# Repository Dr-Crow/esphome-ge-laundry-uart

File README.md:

# ESPHome GE Laundry UART

Local Home Assistant control and monitoring for compatible GE appliances through ESPHome and the appliance's GEA serial bus.

> [!WARNING]
> The appliance uses an 8P8C modular connector that looks like Ethernet, but it is **not Ethernet**. Do not connect it to network equipment.

The project began as an effort to integrate a GE washer and dryer with Home Assistant. An ESP32 powered by the appliance communication port reports information such as remaining time and cycle completion through ESPHome. Early work involved researching the GEA2 and GEA3 protocols and the U+ Connect module; later, [GE Appliances](https://github.com/geappliances) and [FirstBuild](https://firstbuild.com/inventions/home-assistant-adapter/) published additional hardware and protocol information. The maintained ESPHome implementation now lives in [mguaylam/esphome-gea](https://github.com/mguaylam/esphome-gea), while this repository provides compatible hardware, reference configurations, manufacturing files, and enclosures.

## Getting started

### I already have a board

Follow the [firmware setup guide](firmware/README.md) to choose a GEA2 or GEA3 configuration, flash the board, connect it to Home Assistant, and check the status LEDs. The [Rev 2 enclosure](case/rev2/README.md) includes ready-to-print files.

### I want to review a new board

The selected development focus is the socketed C3/C6 Rev3C with both appliance inputs, automatic priority and rated protection. This integration includes all seven editable board revisions, eight firmware profiles, native validation and the [illustrated Rev3C ordering guide](pcb/rev3c/ORDERING.md). Start with the [current comparison and validation](docs/revision-comparison/README.md), [exact source handoff](docs/revision-comparison/HANDOFF.md) and [finish registry](docs/revision-comparison/FINISH-PLAN.md).

Fresh pinned KiCad 9.0.9 ERC/DRC and intended-rule checks pass for all seven revisions. The [Rev3C stencil correction](pcb/rev3c/STENCIL-REVIEW.md) removes unintended drill-marker openings. Native/CAM agreement is separate from supplier process, appliance power and physical qualification. The corrected Rev3C trio has refreshed October 5 quotes of $134.64 for five or $168.92 for ten assembled carriers, before shipping, tax and XIAO modules; Rev2.2's old $78.07 quote is historical.

Older boards and the complete change history are listed in the [PCB revision index](pcb/README.md). Hardware contributors should also read the [contribution guide](CONTRIBUTING.md).

For the proposed USB-C revisions, see the [board and enclosure comparison](docs/revision-comparison/README.md), including assembled-board estimates and views from several angles. The [project handoff](docs/revision-comparison/HANDOFF.md) records the development branches and remaining work.

## Related projects

- [GE Appliances organization](https://github.com/geappliances)
- [FirstBuild Home Assistant adapter](https://firstbuild.com/inventions/home-assistant-adapter/)
- [puddly/casserole](https://github.com/puddly/casserole)
- [GEMakers/green-bean](https://github.com/GEMakers/green-bean)
- [doitaljosh/gea-interface-board](https://github.com/doitaljosh/gea-interface-board)
- [doitaljosh/ge-appliances-re](https://github.com/doitaljosh/ge-appliances-re)
- [doitaljosh/geabus-documentation](https://github.com/doitaljosh/geabus-documentation)
- [simbaja/gehome](https://github.com/simbaja/gehome)
- [GE Appliances Home Assistant adapter](https://github.com/geappliances/home-assistant-adapter)
- [GE Appliances Home Assistant examples](https://github.com/geappliances/home-assistant-examples)
- [GE Appliances Home Assistant bridge](https://github.com/geappliances/home-assistant-bridge)

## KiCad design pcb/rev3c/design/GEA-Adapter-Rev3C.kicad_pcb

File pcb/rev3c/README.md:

# Selected Rev3C prototype: shared XIAO C3/C6 carrier

D14/D15 now use the reviewed 1 A STPS140Z input OR diode; numbered nets and board routing are retained. [Current part-repair evidence](validation/INPUT-DIODE-REPAIR.md) distinguishes this new source from earlier validation and quote snapshots. Exact new-source checks and supplier matching remain required.

The selected development design uses two **TPS1H200A 40 V-rated switches**, 33 V resettable input fuses, and coordinated review of both GE power branches. It preserves PIN1 and PIN3 inputs, automatic PIN1 priority, the AP63205 buck and all C3/C6 side-header functions. C3 is the first implementation focus; C6 firmware and mechanical flexibility remain. Selection does not qualify the appliance supply, surge energy, loaded startup, thermal behavior or enclosure.

The switch change adds voltage margin against the conditional 26 V SMF16A clamp example that exceeds the former TPS22810’s 20 V absolute input limit. It does not give the entire carrier a 40 V rating or prove that a GE appliance produces that pulse. Read the [rated-input review](RATED-SWITCH-OPTION.md) and [qualification gates](POWER-QUALIFICATION.md).

[PCB revision index](../README.md) · [Gate repair](GATE-PROTECTION.md) · [Power qualification](POWER-QUALIFICATION.md) · [Antenna review](ANTENNA-REVIEW.md) · [Shared firmware](../../firmware/shared-rev3c/README.md)

## Preserved hardware

- Original 99 × 40 mm outline, four copper layers and 1.6 mm board thickness
- Mounting datums at (4.5, 33) and (94, 35) mm
- Factory-populated `J5`/`J6` HCTL PM254-1-07-Z-8.5 female 1×7 sockets and all 14 side-header functions
- GEA2/GEA3 interfaces, LEDs, pull-ups and `JP1`'s default 1–2 bridge
- Both original input branches, corrected reverse-FET/gate networks, selected rated load switches, diode isolation, common AP63205 buck and automatic PIN1 priority

The shared-source omissions are `J2` and `D19`; neither GE power input is removed. The local C6 antenna change adds an all-layer copper exclusion at x77.0–80.9, y11.8–19.2 mm and minimal reroutes of `GEA2_RX`, `GEA2_MCU_TX` and `BOOT_SEL`. The selected rated-switch design preserves the original selection and conversion topology. See the [antenna review](ANTENNA-REVIEW.md) for geometry and limits.

The [KiCad project](design/GEA-Adapter-Rev3C.kicad_pro), [schematic](design/GEA-Adapter-Rev3C.kicad_sch) and [PCB](design/GEA-Adapter-Rev3C.kicad_pcb) are editable review sources. Restoration starts from public Rev3C commit `38d94d3dc7c41692e3c41710ec33b9f6e0c38b3e` and recovered shared schematic blob `2799d9e3f023144f684d708297805eed4f355355`.

## Module and firmware selection

The side-header functions match the [XIAO ESP32-C3](https://wiki.seeedstudio.com/XIAO_ESP32C3_Getting_Started/) and [XIAO ESP32-C6](https://wiki.seeedstudio.com/xiao_esp32c6_getting_started/) references. The module is supplied separately from the assembled carrier. Use a module with all 14 header pins installed, and verify its actual revision, header mating depth and retention before use. This interface review does not establish compatibility with other XIAO models.

The [four shared firmware profiles](../../firmware/shared-rev3c/README.md) cover C3/C6 and GEA2/GEA3. Their GPIO numbers differ by module; the recovered eight YAML sources are unchanged. Keep `JP1` at 1–2 for these GEA2 profiles. The alternate 2–3 position changes TX and reaches C3 BOOT; the corresponding C6 D9 pin is GPIO20, not C6 BOOT.

Insert or remove the module only with all power disconnected. Seat all 14 pins without reversal or row offset; the sockets are unkeyed. Match the module USB connector to the carrier's right edge and orientation mark. Recovery uses the module's own BOOT/RESET buttons and native USB. There is no populated carrier recovery header or auxiliary 5 V recovery input.

## Power and qualification

PIN1 and PIN3 from one appliance are two internally selected input branches. Disconnect the appliance cable before attaching powered USB, and remove USB before appliance use. Both reviewed modules connect side-header VBUS directly to USB receptacle VBUS; carrier diodes do not isolate a connected USB host. Keep UART VCC disconnected. Use module 3V3 only as its output. Do not attach a battery within the reviewed load budget.

The corrected reverse-FET/source-referenced gate networks remain. The rated switches address the old switch/clamp rating mismatch in a bounded positive-pulse comparison, and PIN3 gains its matching TVS. Whole-chain transient/energy/differential limits, source current, current-limit/retry effects, thermal behavior and both modules' nominal5 V loaded startup remain open in [POWER-QUALIFICATION.md](POWER-QUALIFICATION.md). Automatic priority detects PIN1 presence rather than useful output power. No universal appliance compatibility is established.

## Review package and cost

Native KiCad 9.0.9 full-severity [ERC](validation/native-kicad-9.0.9-erc.json) and all-track/[parity DRC](validation/native-kicad-9.0.9-drc.json) report 0 violations,0 unconnected items and0 parity differences. The current [rated-switch proof](validation/rated-switch-proof.json) verifies 100 schematic/PCB items,233 pin nets,205 unchanged nonreplacement pin nets, original core functions/outline/mounts/sockets/firmware and0.0 mm² filled copper in the antenna exclusion on all four layers. The historical restoration/gate proofs describe their frozen checkpoints, not the current rated design's full delta.

The regenerated [BOM](manufacturing/BOM-GEA-Adapter-Rev3C.csv) and [CPL](manufacturing/CPL-GEA-Adapter-Rev3C.csv) each contain 83 matching fitted references,80−C22/C23+R38/R39/R40/R41/D20. The module is supplied separately; DNI D8 stays excluded. The native [Gerber/drill ZIP](manufacturing/GERBER-GEA-Adapter-Rev3C.zip) contains 14 members. The [stencil review](STENCIL-REVIEW.md) removes unintended drill-marker openings while preserving existing SMT apertures; D8's two remaining paste apertures need assembler review. [Schematic](validation/schematic.pdf), [PTH](validation/pth-drill-map.pdf) and [NPTH](validation/npth-drill-map.pdf) review PDFs are refreshed.

Current copper views: [front](images/rev3c-copper-f-cu.svg), [inner ground](images/rev3c-copper-in1-cu.svg), [inner routing](images/rev3c-copper-in2-cu.svg), [bottom](images/rev3c-copper-b-cu.svg). Current native partial previews: [C3 top](images/rev3c-render-top.png), [bottom](images/rev3c-render-bottom.png), [C3 oblique](images/rev3c-render-oblique.png), [C6 alternative](images/rev3c-render-c6-oblique.png). The [component model accuracy checkpoint](MODEL-ACCURACY.md) explains the revision-specific official PCB-derived C3/C6 geometry, generic USB/package substitutions, omitted module parts, drawing-based RJ45/socket detail and provisional installed height. Complete manufacturer assembly CAD was not verified; shield/buttons/antenna/male headers are omitted; a separately registered nominal U.FL reference is included and switch/PPTC maximum envelopes remain. Actual pixels were inspected. The [electrical preservation receipt](validation/component-model-electrical-preservation.json) proves that this model lane leaves all electrical source, manufacturing files and firmware unchanged.

Complete exact-part JLCPCB quotes refreshed on October 5, 2026 against the current stencil-corrected trio are **$134.64 for five assembled carriers** and **$168.92 for ten**, before shipping, tax and separately supplied XIAO modules. The source-corrected 80-part baseline was $130.39/$160.37 under the same settings, making the selected design about **$0.85 more per carrier**. All 83 references, including RJ45 and sockets, matched; these are price/availability checks rather than placement or manufacturing approval.

Use the illustrated [JLCPCB quote and ordering guide](ORDERING.md) for the matching Gerber/BOM/CPL trio, exact file hashes, observed settings and review steps. Never mix the selected 83-reference files with the historical baseline. D16/D17 use reviewed MCC BZT52C12-TP/C668891; R40/R41 use the exact 100 kΩ resistor under stocked C149504. The [clamp comparison](RATED-SWITCH-OPTION.md#reviewed-gate-clamp-sourcing-correction) retains MCC’s impedance, temperature and transient limits. BOM/CPL bytes remain the reviewed files; the current Gerber ZIP has the stencil correction and its fresh [supplier quote receipt](validation/JLCPCB-QUOTE-2026-10-05.json) binds all three hashes. Supplier placement/stencil/process approval remains open.

The selected switches add approximately 86 mV of illustrative path loss at 364 mA and change startup/current-fault behavior. Neither the quote nor a native pass closes the loaded 5 V, current, thermal or transient gates. No order or physical test has been performed.

## Enclosure

The [editable shared enclosure review prototype](../../case/rev3c/README.md) is recovered, with one common base and separate C3/C6 lids. It is not a qualified default: its historical electronic proxies need the current component envelopes, and actual socket height, actuator calibration, printing, retention, USB/RJ45 access, antenna cables and RF remain untested. The original C3-specific case does not qualify C6 fit. Follow the [prototype qualification plan](PROTOTYPE-QUALIFICATION.md) before assembly or powered testing.

The [placement-datum review](validation/PLACEMENT-DATUM-REVIEW.md) corrects J1’s CPL body centre without changing CAD, BOM or rotation. Earlier quote hashes remain historical; actual supplier-library pose/process approval is still required.

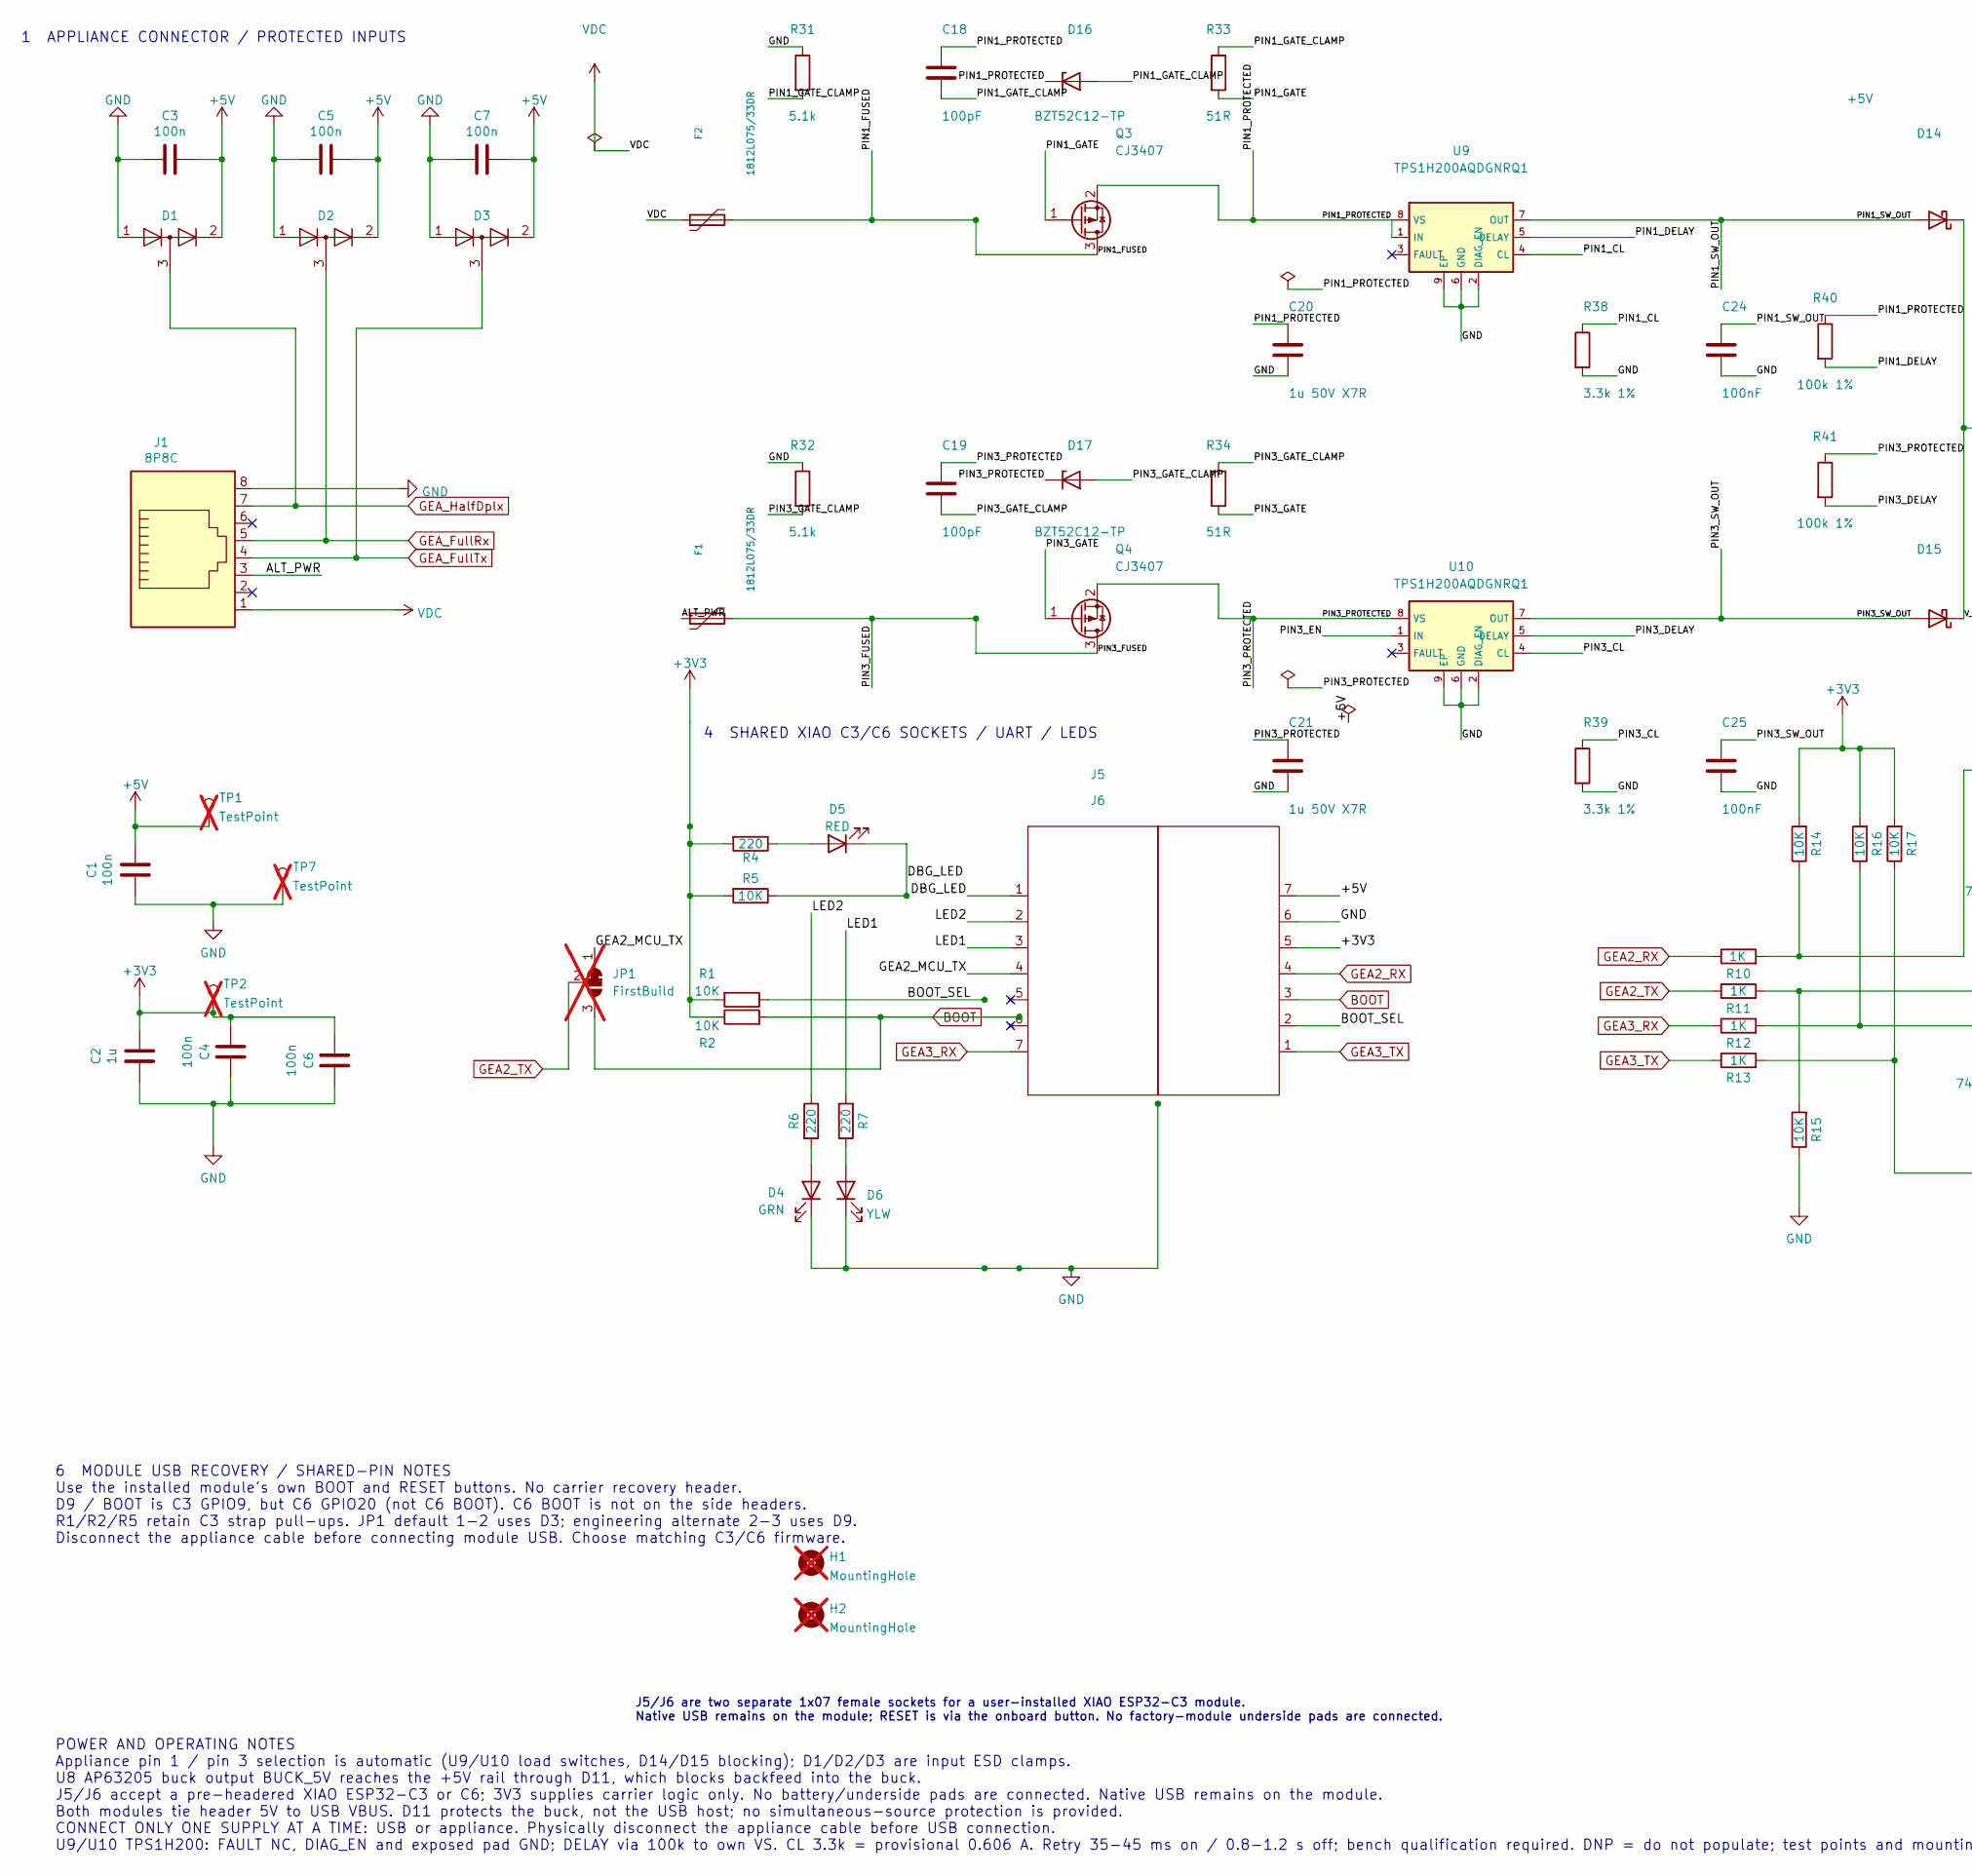
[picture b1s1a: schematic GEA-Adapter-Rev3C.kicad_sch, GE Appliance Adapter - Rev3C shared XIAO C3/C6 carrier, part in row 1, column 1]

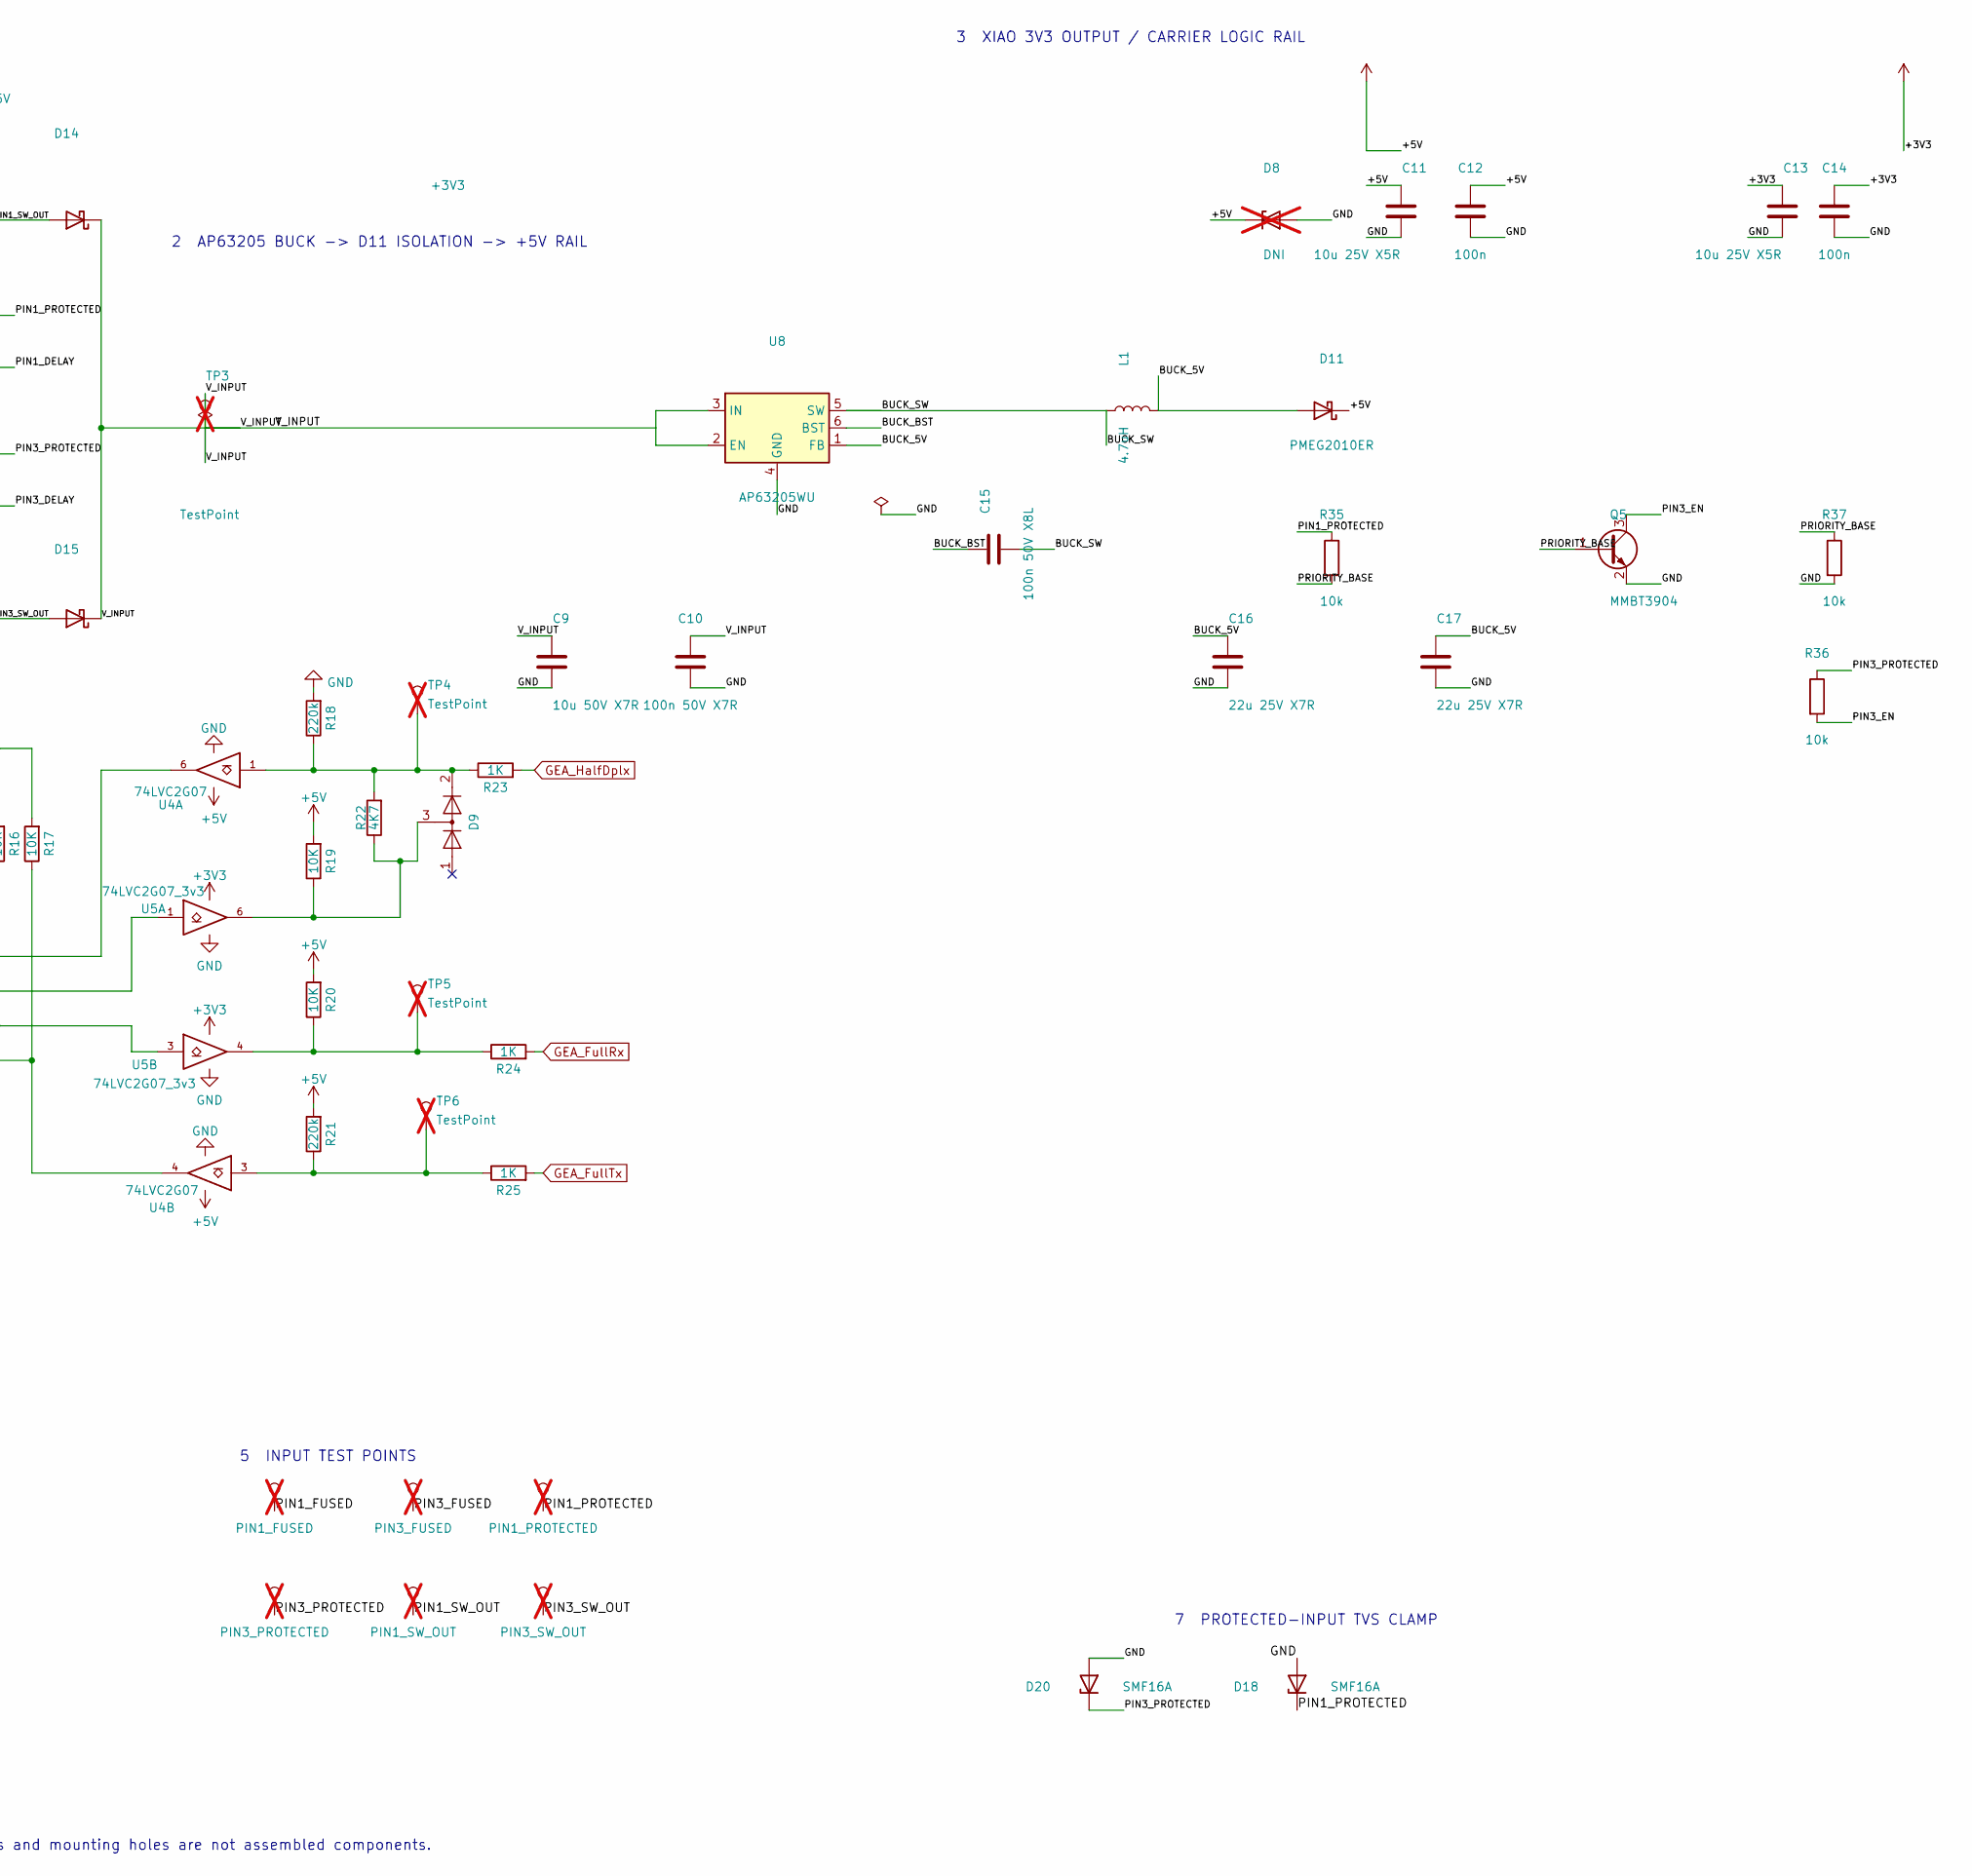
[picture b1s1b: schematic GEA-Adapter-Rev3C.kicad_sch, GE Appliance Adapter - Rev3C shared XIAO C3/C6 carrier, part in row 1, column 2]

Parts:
C1, C3, C4, C5, C6, C7, C12, C14: 100n; C_0805_2012Metric; MPN CC0805KKX7R0BB104; LCSC C106243
C2: 1u; C_0805_2012Metric; MPN CC0805KKX7R9BB105; LCSC C91185
C9: 10u 50V X7R; C_1206_3216Metric; Voltage 50V; MPN 1206B106K500NT; LCSC C303950
C10: 100n 50V X7R; C_0603_1608Metric; Voltage 50V; MPN 0603B104M500NT; LCSC C286510
C11, C13: 10u 25V X5R; C_0805_2012Metric; MPN CL21A106KAYNNNE; LCSC C15850
C15: 100n 50V X8L; C_0603_1608Metric; Voltage 50V; MPN GCM188L81H104KA57D; LCSC C161181
C16, C17: 22u 25V X7R; C_1210_3225Metric; Voltage 25V; Tolerance 10%; MPN CL32B226KAJNNNE; LCSC C309062
C18, C19: 100pF; C_0402_1005Metric; MPN 0402CG101J500NT; LCSC C1546
C20, C21: 1u 50V X7R; C_0805_2012Metric; MPN CC0805KKX7R9BB105; LCSC C91185
C24, C25: 100nF; C_0805_2012Metric; MPN CC0805KKX7R0BB104; LCSC C106243
D1, D2, D3, D9: BAV99; SOT-23; MPN BAV99,215; LCSC C2500
D4: GRN; LED_0805_2012Metric; MPN KT-0805G; LCSC C2297
D5: RED; LED_0805_2012Metric; MPN NCD0805R1; LCSC C84256
D6: YLW; LED_0805_2012Metric; MPN KT-0805Y; LCSC C2296
D8: DNI; D_SOD-123; not fitted
D11: PMEG2010ER; Nexperia_CFP3_SOD-123W; MPN PMEG2010ER,115; LCSC C82288
D14, D15: STPS140Z; D_SOD-123; MPN STPS140Z; LCSC C155662
D16, D17: BZT52C12-TP; D_SOD-123; MPN BZT52C12-TP; LCSC C668891
D18, D20: SMF16A; D_SOD-123F; MPN SMF16A; LCSC C399290
F1, F2: 1812L075/33DR; Fuse_Littelfuse_1812L_Recommended; MPN 1812L075/33DR; LCSC C151170
H1, H2: MountingHole; MountingHole_3.2mm_M3_DIN965; not fitted
J1: 8P8C; RJ45_EVERCOM_5301-8P8C_Horizontal; MPN 5301-8P8C; LCSC C3097717
J5: Socket_XIAO_A; Socket_1x07_P2.54mm_HCTL_PM254; MPN PM254-1-07-Z-8.5; LCSC C2897370
J6: Socket_XIAO_B; Socket_1x07_P2.54mm_HCTL_PM254; MPN PM254-1-07-Z-8.5; LCSC C2897370
JP1: FirstBuild; SolderJumper-3_P1.3mm_Bridged12_RoundedPad1.0x1.5mm_NumberL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; not fitted
L1: 4.7uH; L_Panasonic_PCC-M0530M; MPN ETQP3M4R7KVP; LCSC C412309
Q3, Q4: CJ3407; SOT-23; MPN CJ3407; LCSC C15903
Q5: MMBT3904; SOT-23; MPN MMBT3904; LCSC C20526
R1, R2, R5, R14, R15, R16, R17, R19, R20: 10K; R_0805_2012Metric; MPN 0805W8F1002T5E; LCSC C17414
R4, R6, R7: 220; R_0805_2012Metric; MPN 0805W8F2200T5E; LCSC C17557
R10, R11, R12, R13, R23, R24, R25: 1K; R_0805_2012Metric; MPN 0805W8F1001T5E; LCSC C17513
R18, R21: 220k; R_0805_2012Metric; MPN RTT052203FTP; LCSC C104108
R22: 4K7; R_0805_2012Metric; MPN 0805W8F4701T5E; LCSC C17673
R31, R32: 5.1k; R_0805_2012Metric; MPN 0805W8F5101T5E; LCSC C27834
R33, R34: 51R; R_0805_2012Metric; MPN 0805W8F510JT5E; LCSC C17738
R35, R36, R37: 10k; R_0805_2012Metric; MPN 0805W8F1002T5E; LCSC C17414
R38, R39: 3.3k 1%; R_0603_1608Metric; MPN 0603WAF3301T5E; LCSC C22978
R40, R41: 100k 1%; R_0805_2012Metric; MPN 0805W8F1003T5E; LCSC C149504
TP1, TP2, TP3, TP4, TP5, TP6, TP7: TestPoint; TestPoint_Pad_D2.0mm; not fitted
TP8: PIN1_FUSED; TestPoint_Pad_D1.0mm; not fitted
TP9: PIN3_FUSED; TestPoint_Pad_D1.0mm; not fitted
TP10: PIN1_PROTECTED; TestPoint_Pad_D1.0mm; not fitted
TP11: PIN3_PROTECTED; TestPoint_Pad_D1.0mm; not fitted
TP12: PIN1_SW_OUT; TestPoint_Pad_D1.0mm; not fitted
TP13: PIN3_SW_OUT; TestPoint_Pad_D1.0mm; not fitted
U4: 74LVC2G07; SOT-23-6; MPN 74LVC2G07W6-7; LCSC C151607
U5: 74LVC2G07_3v3; SOT-23-6; MPN 74LVC2G07W6-7; LCSC C151607
U8: AP63205WU; TSOT-23-6; MPN AP63205WU-7; LCSC C2071056
U9, U10: TPS1H200AQDGNRQ1; TPS1H200A_DGN0008K_TI_RevE; MPN TPS1H200AQDGNRQ1; LCSC C2653785

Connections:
+3V3: C2.1, C4.2, C6.2, C13.1, C14.2, J6.5 (3V3_OUT), R1.2, R2.1, R4.2, R5.2, R14.2, R16.2, R17.2, TP2.1, U5.5 (+3V3)
+5V: C1.1, C3.1, C5.1, C7.1, C11.1, C12.2, D1.2 (A), D2.2 (A), D3.2 (A), D8.1 (K), D11.1 (K), J6.7 (VBUS), R19.2, R20.2, R21.2, TP1.1, U4.5 (VCC)
/ALT_PWR: F1.1, J1.3
/BOOT_SEL: J6.2 (BOOT_SEL), R1.1
/BUCK_5V: C16.1, C17.1, D11.2 (A), L1.2, U8.1 (FB)
/BUCK_BST: C15.1, U8.6 (BST)
/BUCK_SW: C15.2, L1.1, U8.5 (SW)
/DBG_LED: D5.1 (K), J5.1 (DBG_LED), R5.1
/GEA2_MCU_TX: J5.4 (GEA2_MCU_TX), JP1.1 (A)
/LED1: J5.3 (LED1), R7.2
/LED2: J5.2 (LED2), R6.1
/PIN1_CL: R38.1, U9.4 (CL)
/PIN1_DELAY: R40.2, U9.5 (DELAY)
/PIN1_FUSED: F2.2, Q3.3 (D), TP8.1
/PIN1_GATE: Q3.1 (G), R33.2
/PIN1_GATE_CLAMP: C18.2, D16.2 (A), R31.2, R33.1
/PIN1_PROTECTED: C18.1, C20.1, D16.1 (K), D18.1 (K), Q3.2 (S), R35.1, R40.1, TP10.1, U9.1 (IN), U9.8 (VS)
/PIN1_SW_OUT: C24.1, D14.2 (A), TP12.1, U9.7 (OUT)
/PIN3_CL: R39.1, U10.4 (CL)
/PIN3_DELAY: R41.2, U10.5 (DELAY)
/PIN3_EN: Q5.3 (C), R36.2, U10.1 (IN)
/PIN3_FUSED: F1.2, Q4.3 (D), TP9.1
/PIN3_GATE: Q4.1 (G), R34.2
/PIN3_GATE_CLAMP: C19.2, D17.2 (A), R32.2, R34.1
/PIN3_PROTECTED: C19.1, C21.1, D17.1 (K), D20.1 (K), Q4.2 (S), R36.1, R41.1, TP11.1, U10.8 (VS)
/PIN3_SW_OUT: C25.1, D15.2 (A), TP13.1, U10.7 (OUT)
/PRIORITY_BASE: Q5.1 (B), R35.2, R37.1
/V_INPUT: C9.1, C10.2, D14.1 (K), D15.1 (K), TP3.1, U8.2 (EN), U8.3 (IN)
BOOT: J6.3 (BOOT), JP1.3 (B), R2.2
GEA2_RX: J6.4 (GEA2_RX), R10.1
GEA2_TX: JP1.2 (C), R11.1
GEA3_RX: J5.7 (GEA3_RX), R12.1
GEA3_TX: J6.1 (GEA3_TX), R13.1
GEA_FullRx: D2.3 (K), J1.5, R24.2
GEA_FullTx: D3.3 (K), J1.4, R25.2
GEA_HalfDplx: D1.3 (K), J1.7, R23.2
GND: C1.2, C2.2, C3.2, C4.1, C5.2, C6.1, C7.2, C9.2, C10.1, C11.2, C12.1, C13.2, C14.1, C16.2, C17.2, C20.2, C21.2, C24.2, C25.2, D1.1 (K), D2.1 (K), D3.1 (K), D4.1 (K), D6.1 (K), D8.2 (A), D18.2 (A), D20.2 (A), J1.8, J6.6 (GND), Q5.2 (E), R15.1, R18.2, R31.1, R32.1, R37.2, R38.2, R39.2, TP7.1, U4.2 (GND), U5.2 (GND), U8.4 (GND), U9.2 (DIAG_EN), U9.6 (GND), U9.9 (EP), U10.2 (DIAG_EN), U10.6 (GND), U10.9 (EP)
unnamed: D4.2 (A), R6.2
unnamed: D5.2 (A), R4.1
unnamed: D6.2 (A), R7.1
unnamed: D9.3 (K), R19.1, R22.1, U5.6
unnamed: D9.2 (A), R18.1, R22.2, R23.1, TP4.1, U4.1
unnamed: R10.2, R14.1, U4.6
unnamed: R11.2, R15.2, U5.1
unnamed: R12.2, R16.1, U5.3
unnamed: R13.2, R17.1, U4.4
unnamed: R20.1, R24.1, TP5.1, U5.4
unnamed: R21.1, R25.1, TP6.1, U4.3
VDC: F2.1, J1.1

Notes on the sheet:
1 APPLIANCE CONNECTOR / PROTECTED INPUTS
2 AP63205 BUCK -> D11 ISOLATION -> +5V RAIL
3 XIAO 3V3 OUTPUT / CARRIER LOGIC RAIL
4 SHARED XIAO C3/C6 SOCKETS / UART / LEDS
6 MODULE USB RECOVERY / SHARED-PIN NOTES Use the installed module's own BOOT and RESET buttons. No carrier recovery header. D9 / BOOT is C3 GPIO9, but C6 GPIO20 (not C6 BOOT). C6 BOOT is not on the side headers. R1/R2/R5 retain C3 strap pull-ups. JP1 default 1-2 uses D3; engineering alternate 2-3 u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
7 PROTECTED-INPUT TVS CLAMP
5 INPUT TEST POINTS
POWER AND OPERATING NOTES Appliance pin 1 / pin 3 selection is automatic (U9/U10 load switches, D14/D15 blocking); D1/D2/D3 are input ESD clamps. U8 AP63205 buck output BUCK_5V reaches the +5V rail through D11, which blocks backfeed into the buck. J5/J6 accept a pre-headered XIAO ESP32-C3 or C6; 3V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
J5/J6 are two separate 1x07 female sockets for a user-installed XIAO ESP32-C3 module. Native USB remains on the module; RESET is via the onboard button. No factory-module underside pads are connected.

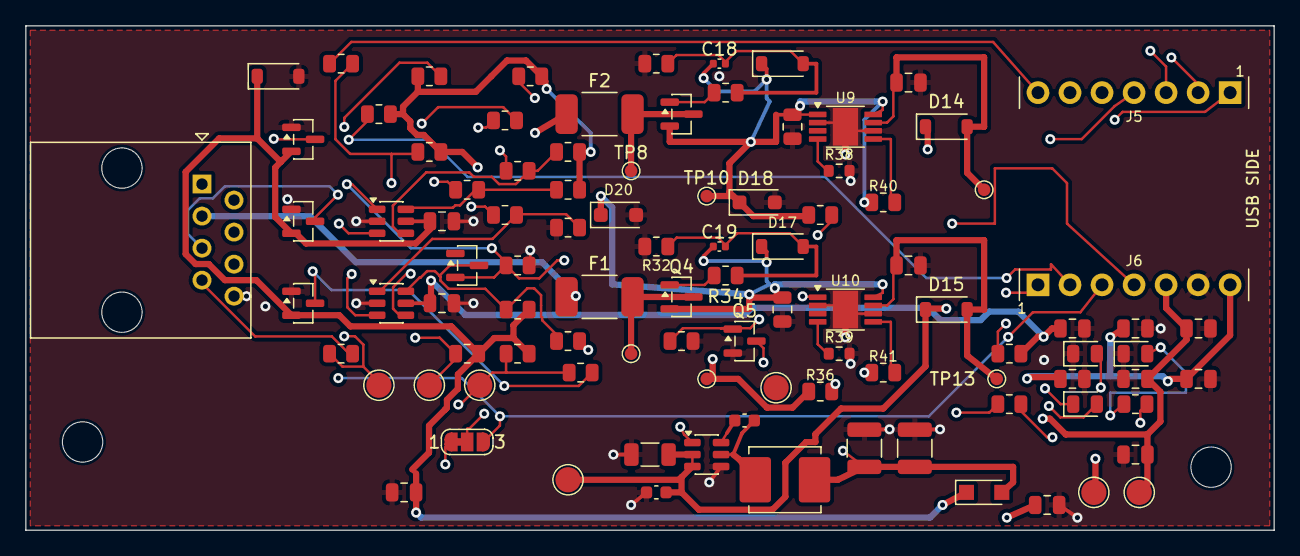
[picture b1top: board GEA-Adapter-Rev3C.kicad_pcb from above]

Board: 4 copper layers, 99.0 x 40.0 mm, 100 parts (0 on the bottom side), 49 nets.

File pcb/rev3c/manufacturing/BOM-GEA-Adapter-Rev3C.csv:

"Comment","Designator","Footprint","LCSC Part #"
"100n","C1","Capacitor_SMD:C_0805_2012Metric","C106243"
"1u","C2","Capacitor_SMD:C_0805_2012Metric","C91185"
"100n","C3","Capacitor_SMD:C_0805_2012Metric","C106243"
"100n","C4","Capacitor_SMD:C_0805_2012Metric","C106243"
"100n","C5","Capacitor_SMD:C_0805_2012Metric","C106243"
"100n","C6","Capacitor_SMD:C_0805_2012Metric","C106243"
"100n","C7","Capacitor_SMD:C_0805_2012Metric","C106243"
"10u 50V X7R","C9","Capacitor_SMD:C_1206_3216Metric","C303950"
"100n 50V X7R","C10","Capacitor_SMD:C_0603_1608Metric","C286510"
"10u 25V X5R","C11","Capacitor_SMD:C_0805_2012Metric","C15850"
"100n","C12","Capacitor_SMD:C_0805_2012Metric","C106243"
"10u 25V X5R","C13","Capacitor_SMD:C_0805_2012Metric","C15850"
"100n","C14","Capacitor_SMD:C_0805_2012Metric","C106243"
"100n 50V X8L","C15","Capacitor_SMD:C_0603_1608Metric","C161181"
"22u 25V X7R","C16","Capacitor_SMD:C_1210_3225Metric","C309062"
"22u 25V X7R","C17","Capacitor_SMD:C_1210_3225Metric","C309062"
"100pF","C18","Capacitor_SMD:C_0402_1005Metric","C1546"
"100pF","C19","Capacitor_SMD:C_0402_1005Metric","C1546"
"1u 50V X7R","C20","Capacitor_SMD:C_0805_2012Metric","C91185"
"1u 50V X7R","C21","Capacitor_SMD:C_0805_2012Metric","C91185"
"100nF","C24","Capacitor_SMD:C_0805_2012Metric","C106243"
"100nF","C25","Capacitor_SMD:C_0805_2012Metric","C106243"
"BAV99","D1","Package_TO_SOT_SMD:SOT-23","C2500"
"BAV99","D2","Package_TO_SOT_SMD:SOT-23","C2500"
"BAV99","D3","Package_TO_SOT_SMD:SOT-23","C2500"
"GRN","D4","LED_SMD:LED_0805_2012Metric","C2297"
"RED","D5","LED_SMD:LED_0805_2012Metric","C84256"
"YLW","D6","LED_SMD:LED_0805_2012Metric","C2296"
"BAV99","D9","Package_TO_SOT_SMD:SOT-23","C2500"
"PMEG2010ER","D11","Diode_SMD:Nexperia_CFP3_SOD-123W","C82288"
"STPS140Z","D14","Diode_SMD:D_SOD-123","C155662"
"STPS140Z","D15","Diode_SMD:D_SOD-123","C155662"
"BZT52C12-TP","D16","Diode_SMD:D_SOD-123","C668891"
"BZT52C12-TP","D17","Diode_SMD:D_SOD-123","C668891"
"SMF16A","D18","Diode_SMD:D_SOD-123F","C399290"
"SMF16A","D20","Diode_SMD:D_SOD-123F","C399290"
"1812L075/33DR","F1","GEA_Rev3C:Fuse_Littelfuse_1812L_Recommended","C151170"
"1812L075/33DR","F2","GEA_Rev3C:Fuse_Littelfuse_1812L_Recommended","C151170"
"8P8C","J1","OnionStraws:RJ45_EVERCOM_5301-8P8C_Horizontal","C3097717"
"Socket_XIAO_A","J5","GEA_Rev3C:Socket_1x07_P2.54mm_HCTL_PM254","C2897370"
"Socket_XIAO_B","J6","GEA_Rev3C:Socket_1x07_P2.54mm_HCTL_PM254","C2897370"
"4.7uH","L1","Inductor_SMD:L_Panasonic_PCC-M0530M","C412309"
"CJ3407","Q3","Package_TO_SOT_SMD:SOT-23","C15903"
"CJ3407","Q4","Package_TO_SOT_SMD:SOT-23","C15903"
"MMBT3904","Q5","Package_TO_SOT_SMD:SOT-23","C20526"
"10K","R1","Resistor_SMD:R_0805_2012Metric","C17414"
"10K","R2","Resistor_SMD:R_0805_2012Metric","C17414"
"220","R4","Resistor_SMD:R_0805_2012Metric","C17557"
"10K","R5","Resistor_SMD:R_0805_2012Metric","C17414"
"220","R6","Resistor_SMD:R_0805_2012Metric","C17557"
"220","R7","Resistor_SMD:R_0805_2012Metric","C17557"
"1K","R10","Resistor_SMD:R_0805_2012Metric","C17513"
"1K","R11","Resistor_SMD:R_0805_2012Metric","C17513"
"1K","R12","Resistor_SMD:R_0805_2012Metric","C17513"
"1K","R13","Resistor_SMD:R_0805_2012Metric","C17513"
"10K","R14","Resistor_SMD:R_0805_2012Metric","C17414"
"10K","R15","Resistor_SMD:R_0805_2012Metric","C17414"
"10K","R16","Resistor_SMD:R_0805_2012Metric","C17414"
"10K","R17","Resistor_SMD:R_0805_2012Metric","C17414"
"220k","R18","Resistor_SMD:R_0805_2012Metric","C104108"
"10K","R19","Resistor_SMD:R_0805_2012Metric","C17414"
"10K","R20","Resistor_SMD:R_0805_2012Metric","C17414"
"220k","R21","Resistor_SMD:R_0805_2012Metric","C104108"
"4K7","R22","Resistor_SMD:R_0805_2012Metric","C17673"
"1K","R23","Resistor_SMD:R_0805_2012Metric","C17513"
"1K","R24","Resistor_SMD:R_0805_2012Metric","C17513"
"1K","R25","Resistor_SMD:R_0805_2012Metric","C17513"
"5.1k","R31","Resistor_SMD:R_0805_2012Metric","C27834"
"5.1k","R32","Resistor_SMD:R_0805_2012Metric","C27834"
"51R","R33","Resistor_SMD:R_0805_2012Metric","C17738"
"51R","R34","Resistor_SMD:R_0805_2012Metric","C17738"
"10k","R35","Resistor_SMD:R_0805_2012Metric","C17414"
"10k","R36","Resistor_SMD:R_0805_2012Metric","C17414"
"10k","R37","Resistor_SMD:R_0805_2012Metric","C17414"
"3.3k 1%","R38","Resistor_SMD:R_0603_1608Metric","C22978"
"3.3k 1%","R39","Resistor_SMD:R_0603_1608Metric","C22978"
"100k 1%","R40","Resistor_SMD:R_0805_2012Metric","C149504"
"100k 1%","R41","Resistor_SMD:R_0805_2012Metric","C149504"
"74LVC2G07","U4","Package_TO_SOT_SMD:SOT-23-6","C151607"
"74LVC2G07_3v3","U5","Package_TO_SOT_SMD:SOT-23-6","C151607"
"AP63205WU","U8","Package_TO_SOT_SMD:TSOT-23-6","C2071056"
"TPS1H200AQDGNRQ1","U9","GEA_Rev3C:TPS1H200A_DGN0008K_TI_RevE","C2653785"
"TPS1H200AQDGNRQ1","U10","GEA_Rev3C:TPS1H200A_DGN0008K_TI_RevE","C2653785"
